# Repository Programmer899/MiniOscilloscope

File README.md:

## Mini Oscilloscope
# Description
This is a mini version of an oscilloscope.
It is used to display some incoming readings on an analog pin and showing the results using an oled display as a wave like format.

# How does it work
What you do is connecting the 5V signal cable you want to read to the incoming connection on the board, it is then sent through a voltage regulator, lowering it to a safe 3.3V signal.
The aTTiny3224 then reads that signal on one of it's analog pins, calculate the correct pixel on the display and then store the result as an integer (whole number) using an 8BIT value.

The stored values are then using a specified "screen update frequency" displayed.
This is to allow the incoming signals to be read faster than the screen might be capable of.

# Schematic

# PCB

# Rendered

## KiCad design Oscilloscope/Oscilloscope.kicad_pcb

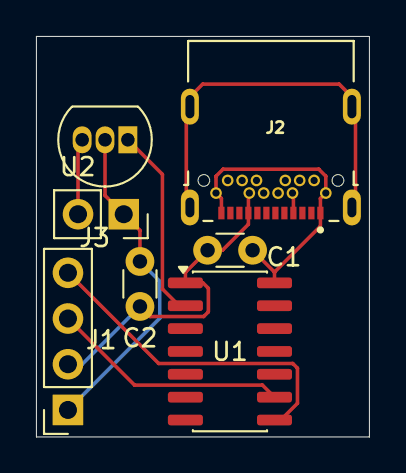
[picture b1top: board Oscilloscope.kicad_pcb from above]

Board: 2 copper layers, 18.5 x 22.2 mm, 7 parts (0 on the bottom side), 6 nets.

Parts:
C1, C2: C; C_Disc_D3.0mm_W1.6mm_P2.50mm
J1: OLED 128x64; PinSocket_1x04_P2.54mm_Vertical
J2: USB_C_Receptacle_PowerOnly_24P; CUI_UJ31-CH-G2-SMT-TR
J3: Signal Jack; PinSocket_1x02_P2.54mm_Vertical
U1: ATtiny3224-SS; SOIC-14_3.9x8.7mm_P1.27mm
U2: Signal regulator; TO-92_Inline

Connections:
GND: C1.1, C2.2, J1.1, J2.A1 (GND), J2.A12 (GND), J2.B1 (GND), J2.B12 (GND), J3.1, U1.14 (GND), U2.2 (GND)
unnamed: J3.2, U2.3 (VI)
SCL: J1.3, U1.9 (PB0)
SDA: J1.4, U1.8 (PB1)
SigIN 3.3V: U1.2 (PA4), U2.1 (VO)
VCC: C1.2, C2.1, J1.2, J2.A4 (VBUS), J2.A9 (VBUS), J2.B4 (VBUS), J2.B9 (VBUS), U1.1 (VCC)
